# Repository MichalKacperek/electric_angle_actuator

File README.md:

# electric_angle_actuator
 PCB for AM4096 encoder with STM32F103RBT6 microcontroller and terminals for DC motor controller based on two L6390D

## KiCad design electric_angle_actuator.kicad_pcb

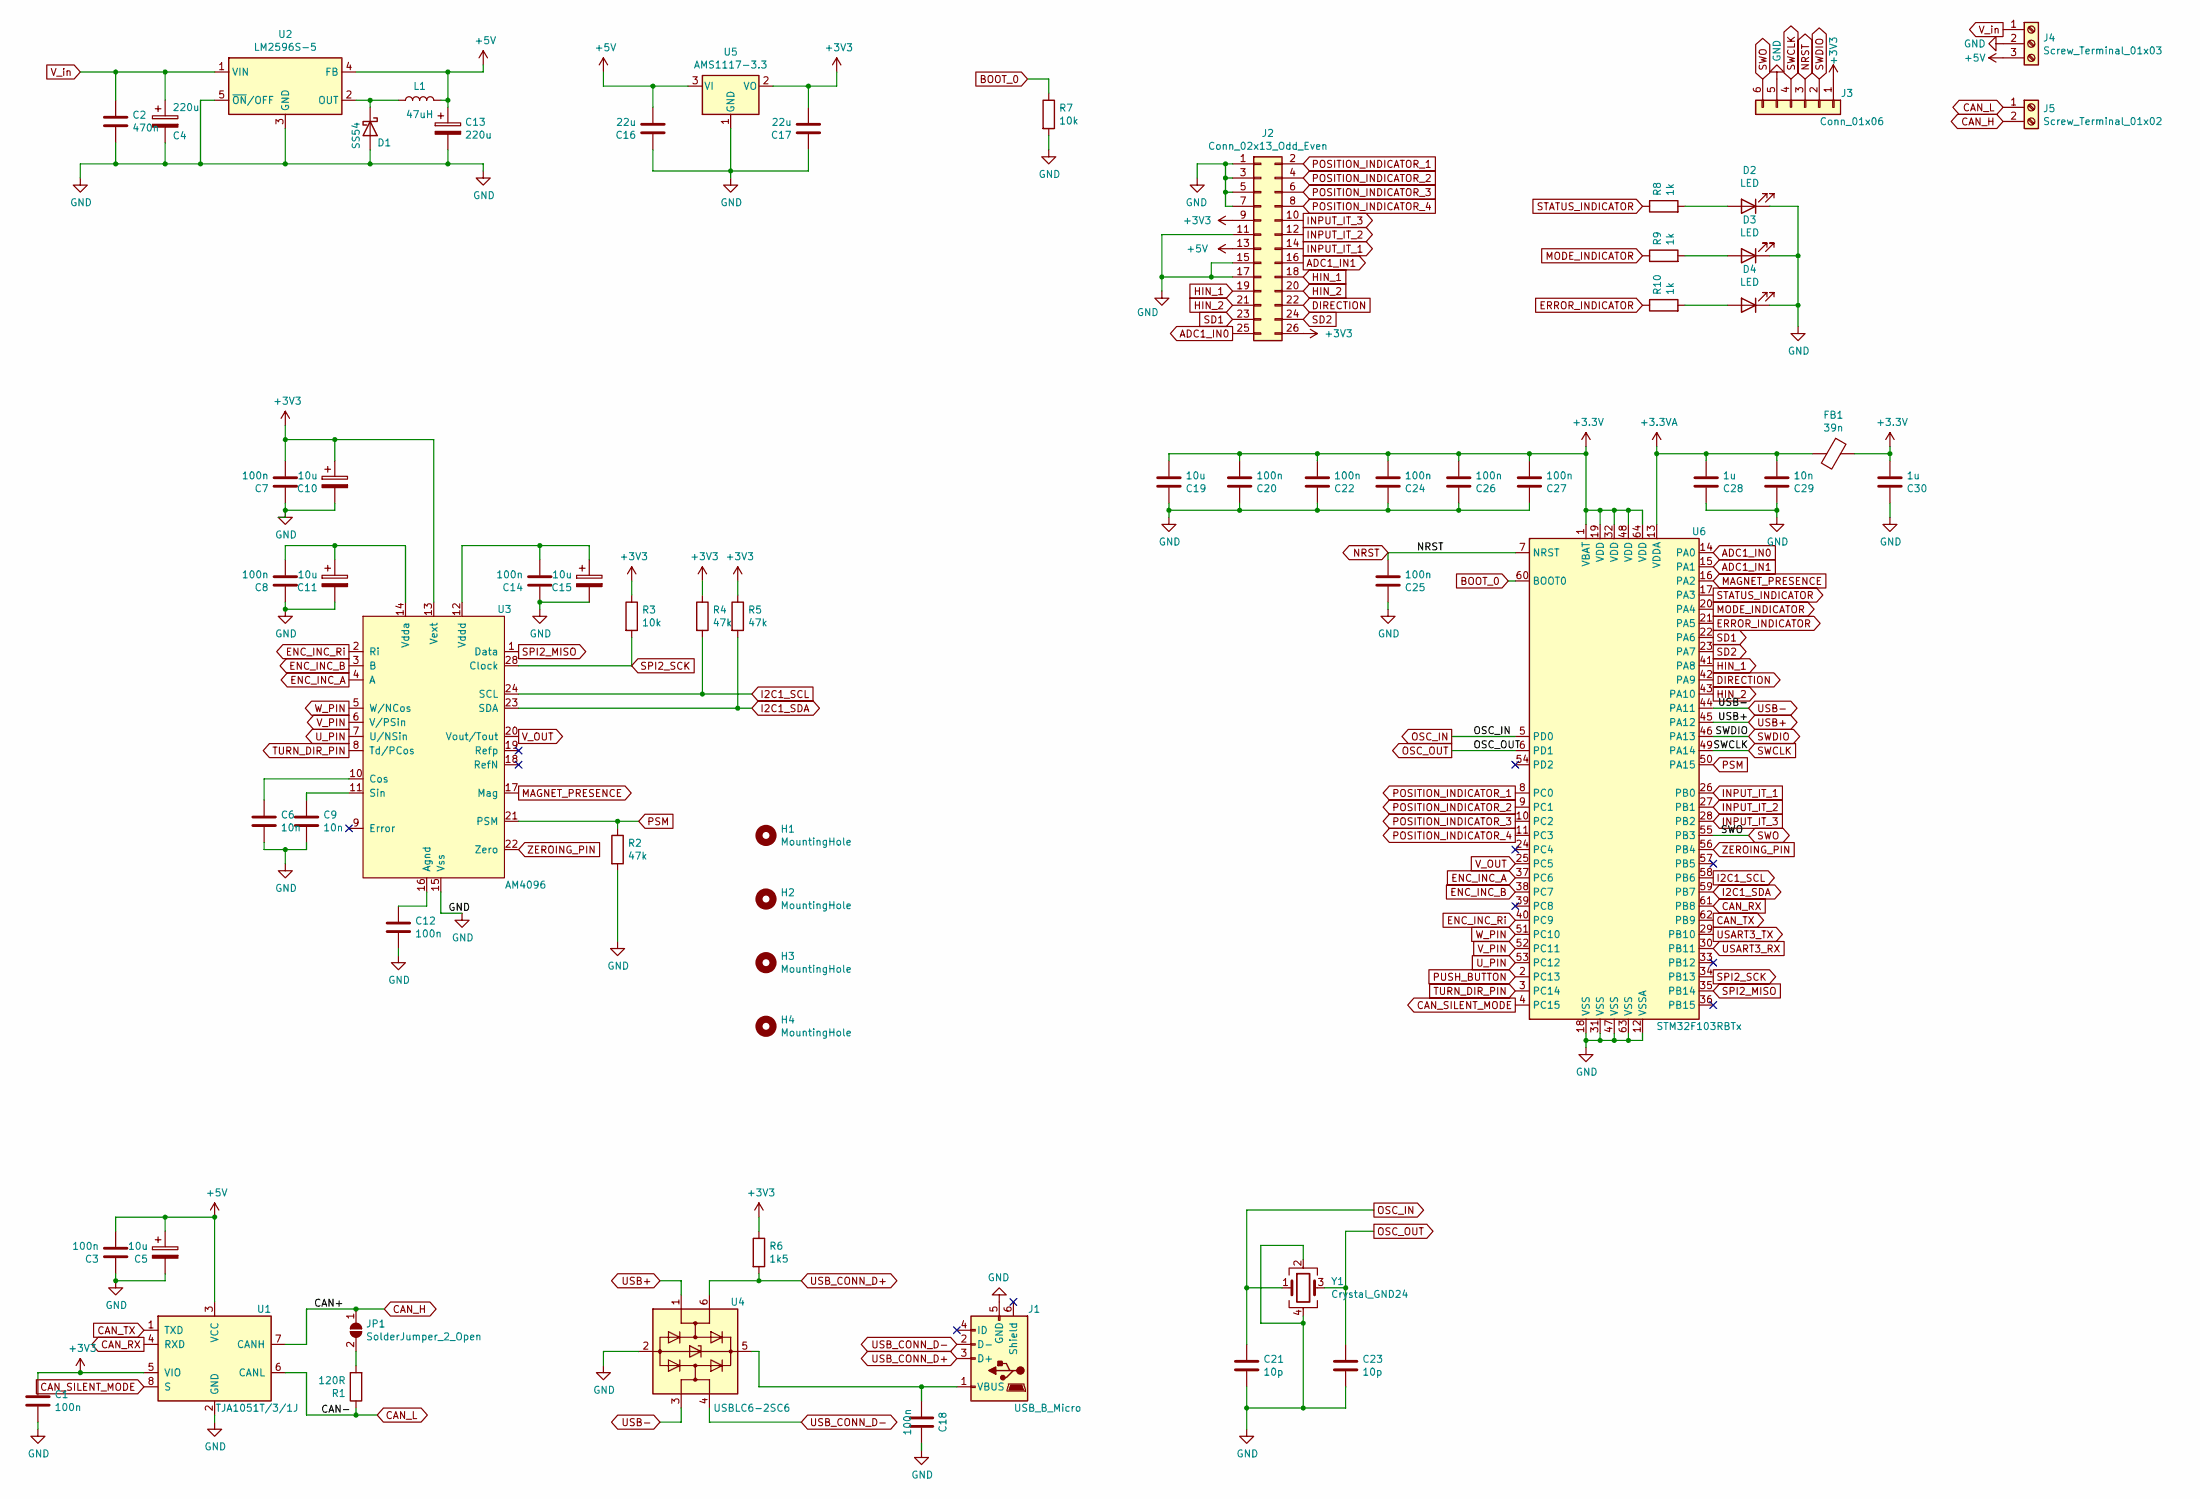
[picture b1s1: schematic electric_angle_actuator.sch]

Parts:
C1, C3, C7, C8, C12, C14, C18, C20, C22, C24, C25, C26, C27: 100n; C_0402_1005Metric; JLCPCB C307331
C2: 470n; C_0805_2012Metric; JLCPCB C13967
C4, C13: 220u; CP_Elec_10x10.5; JLCPCB C2887271
C5, C11: 10u; C_0805_2012Metric; JLCPCB C15850
C6, C9, C29: 10n; C_0402_1005Metric; JLCPCB C15195
C10, C15, C19: 10u; CP_EIA-3216-10_Kemet-I; JLCPCB C7171
C16, C17: 22u; C_1206_3216Metric; JLCPCB C5672
C21, C23: 10p; C_0402_1005Metric; JLCPCB C32949
C28: 1u; C_0805_2012Metric; JLCPCB C28323
C30: 1u; C_0402_1005Metric; JLCPCB C52923
D1: SS54; D_SMA; JLCPCB C22452
D2, D3, D4: LED; LED_0603_1608Metric; JLCPCB C2286
FB1: 39n; L_0402_1005Metric; JLCPCB C26443
H1, H2, H3, H4: MountingHole; MountingHole_2.2mm_M2
J1: USB_B_Micro; USB_Micro-B_Molex-105017-0001; JLCPCB C136000
J2: Conn_02x13_Odd_Even; PinHeader_2x13_P2.54mm_Vertical
J3: Conn_01x06; Tag-Connect_TC2030-IDC-NL_2x03_P1.27mm_Vertical
J4: Screw_Terminal_01x03; TerminalBlock_Phoenix_MKDS-1,5-3-5.08_1x03_P5.08mm_Horizont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
J5: Screw_Terminal_01x02; TerminalBlock_Phoenix_MKDS-1,5-2-5.08_1x02_P5.08mm_Horizont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
JP1: SolderJumper_2_Open; SolderJumper-2_P1.3mm_Open_RoundedPad1.0x1.5mm
L1: 47uH; L_12x12mm_H8mm; JLCPCB CYH127-47UH
R1: 120R; R_0402_1005Metric; JLCPCB C25079
R2, R4, R5: 47k; R_0402_1005Metric; JLCPCB C25792
R3, R7: 10k; R_0402_1005Metric; JLCPCB C25744
R6: 1k5; R_0402_1005Metric; JLCPCB C25867
R8, R9, R10: 1k; R_0402_1005Metric; JLCPCB C11702
U1: TJA1051T/3/1J; SOIC-8_3.9x4.9mm_P1.27mm; JLCPCB C38695
U2: LM2596S-5; TO-263-5_TabPin3; JLCPCB C10002
U3: AM4096; SSOP-28_5.3x10.2mm_P0.65mm
U4: USBLC6-2SC6; SOT-23-6; JLCPCB C7519
U5: AMS1117-3.3; SOT-223-3_TabPin2; JLCPCB C6186
U6: STM32F103RBTx; LQFP-64_10x10mm_P0.5mm; JLCPCB C8735
Y1: Crystal_GND24; Crystal_SMD_3225-4Pin_3.2x2.5mm; JLCPCB C13738

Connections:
+3.3VA: C28.2, C29.2, FB1.2, U6.13 (VDDA)
+5V: C3.2, C5.1, C13.1, C16.2, J2.13, J4.3, L1.2, U1.3 (VCC), U2.4 (FB), U5.3 (VI)
ADC1_IN0: J2.25, U6.14 (PA0)
ADC1_IN1: J2.16, U6.15 (PA1)
BOOT_0: R7.1, U6.60 (BOOT0)
CAN_H: J5.2, JP1.1 (A), U1.7 (CANH)
CAN_L: J5.1, R1.1, U1.6 (CANL)
CAN_RX: U1.4 (RXD), U6.61 (PB8)
CAN_SILENT_MODE: U1.8 (S), U6.4 (PC15)
CAN_TX: U1.1 (TXD), U6.62 (PB9)
DIRECTION: J2.22, U6.42 (PA9)
ENC_INC_A: U3.4 (A), U6.37 (PC6)
ENC_INC_B: U3.3 (B), U6.38 (PC7)
ENC_INC_Ri: U3.2 (Ri), U6.40 (PC9)
ERROR_INDICATOR: R10.1, U6.21 (PA5)
GND: C1.2, C2.2, C3.1, C4.2, C5.2, C6.2, C7.1, C8.1, C9.2, C10.2, C11.2, C12.2, C13.2, C14.1, C15.2, C16.1, C17.1, C18.1, C19.1, C20.1, C21.2, C22.1, C23.2, C24.1, C25.1, C26.1, C27.1, C28.1, C29.1, C30.1, D1.2 (A), D2.1 (K), D3.1 (K), D4.1 (K), J1.5 (GND), J2.1, J2.3, J2.5, J2.7, J2.11, J2.15, J2.17, J3.5, J4.2, R2.2, R7.2, U1.2 (GND), U2.3 (GND), U2.5 (~ON~/OFF), U3.15 (Vss), U4.2 (GND), U5.1 (GND), U6.12 (VSSA), U6.18 (VSS), U6.31 (VSS), U6.47 (VSS), U6.63 (VSS), Y1.2, Y1.4
HIN_1: J2.18, J2.19, U6.41 (PA8)
HIN_2: J2.20, J2.21, U6.43 (PA10)
I2C1_SCL: R4.2, U3.24 (SCL), U6.58 (PB6)
I2C1_SDA: R5.2, U3.23 (SDA), U6.59 (PB7)
INPUT_IT_1: J2.14, U6.26 (PB0)
INPUT_IT_2: J2.12, U6.27 (PB1)
INPUT_IT_3: J2.10, U6.28 (PB2)
MAGNET_PRESENCE: U3.17 (Mag), U6.16 (PA2)
MODE_INDICATOR: R9.1, U6.20 (PA4)
NRST: C25.2, J3.3, U6.7 (NRST)
unnamed: C6.1, U3.10 (Cos)
unnamed: C9.1, U3.11 (Sin)
unnamed: C8.2, C11.1, U3.14 (Vdda)
unnamed: C12.1, U3.16 (Agnd)
unnamed: C14.2, C15.1, U3.12 (Vddd)
unnamed: C18.2, J1.1 (VBUS), U4.5 (VBUS)
unnamed: D1.1 (K), L1.1, U2.2 (OUT)
unnamed: D2.2 (A), R8.2
unnamed: D3.2 (A), R9.2
unnamed: D4.2 (A), R10.2
unnamed: JP1.2 (B), R1.2
OSC_IN: C21.1, U6.5 (PD0), Y1.1
OSC_OUT: C23.1, U6.6 (PD1), Y1.3
POSITION_INDICATOR_1: J2.2, U6.8 (PC0)
POSITION_INDICATOR_2: J2.4, U6.9 (PC1)
POSITION_INDICATOR_3: J2.6, U6.10 (PC2)
POSITION_INDICATOR_4: J2.8, U6.11 (PC3)
PSM: R2.1, U3.21 (PSM), U6.50 (PA15)
PUSH_BUTTON: U6.2 (PC13)
SD1: J2.23, U6.22 (PA6)
SD2: J2.24, U6.23 (PA7)
SPI2_MISO: U3.1 (Data), U6.35 (PB14)
SPI2_SCK: R3.2, U3.28 (Clock), U6.34 (PB13)
STATUS_INDICATOR: R8.1, U6.17 (PA3)
SWCLK: J3.4, U6.49 (PA14)
SWDIO: J3.2, U6.46 (PA13)
SWO: J3.6, U6.55 (PB3)
TURN_DIR_PIN: U3.8 (Td/PCos), U6.3 (PC14)
USART3_RX: U6.30 (PB11)
USART3_TX: U6.29 (PB10)
USB+: U4.1 (I/O1), U6.45 (PA12)
USB-: U4.3 (I/O2), U6.44 (PA11)
USB_CONN_D+: J1.3 (D+), R6.2, U4.6 (I/O1)
USB_CONN_D-: J1.2 (D-), U4.4 (I/O2)
U_PIN: U3.7 (U/NSin), U6.53 (PC12)
V_OUT: U3.20 (Vout/Tout), U6.25 (PC5)
V_PIN: U3.6 (V/PSin), U6.52 (PC11)
V_in: C2.1, C4.1, J4.1, U2.1 (VIN)
W_PIN: U3.5 (W/NCos), U6.51 (PC10)
ZEROING_PIN: U3.22 (Zero), U6.56 (PB4)

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
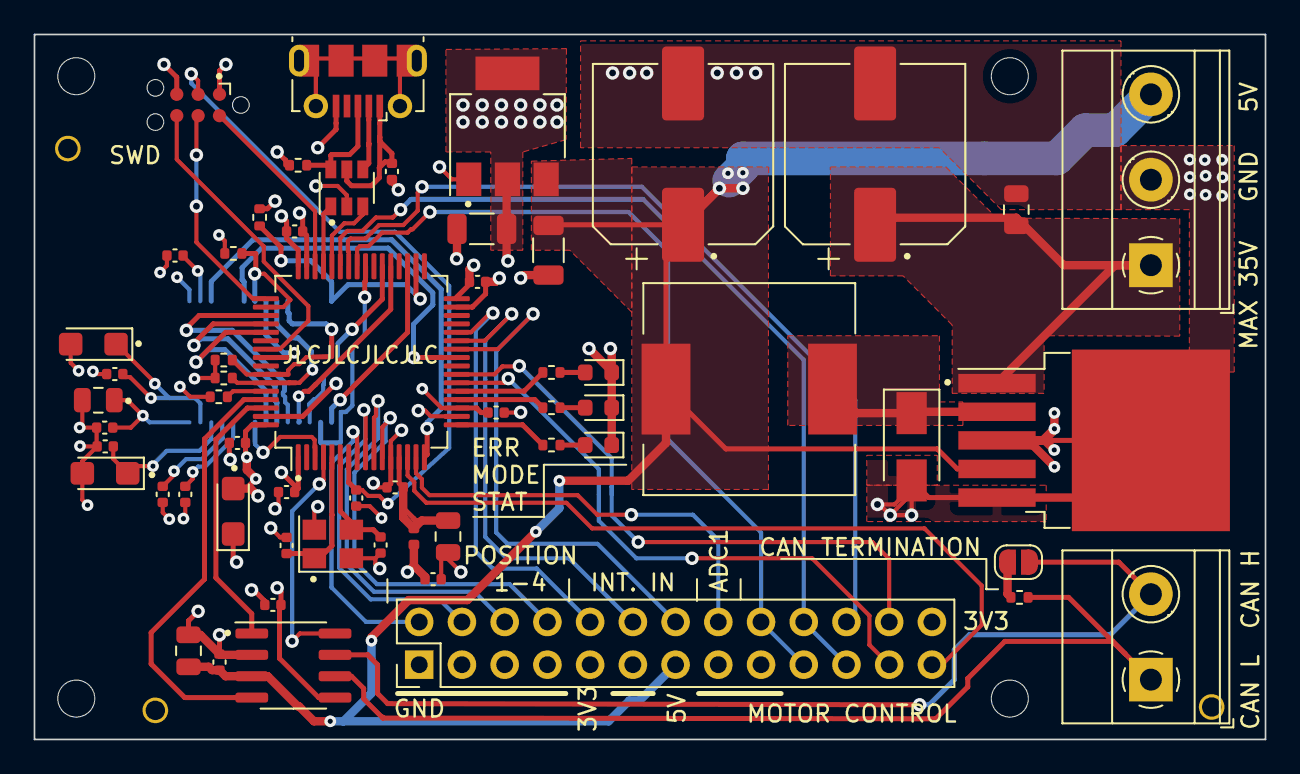
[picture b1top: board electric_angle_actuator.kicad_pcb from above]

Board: 4 copper layers, 73.2 x 41.9 mm, 63 parts (1 on the bottom side), 64 nets.
